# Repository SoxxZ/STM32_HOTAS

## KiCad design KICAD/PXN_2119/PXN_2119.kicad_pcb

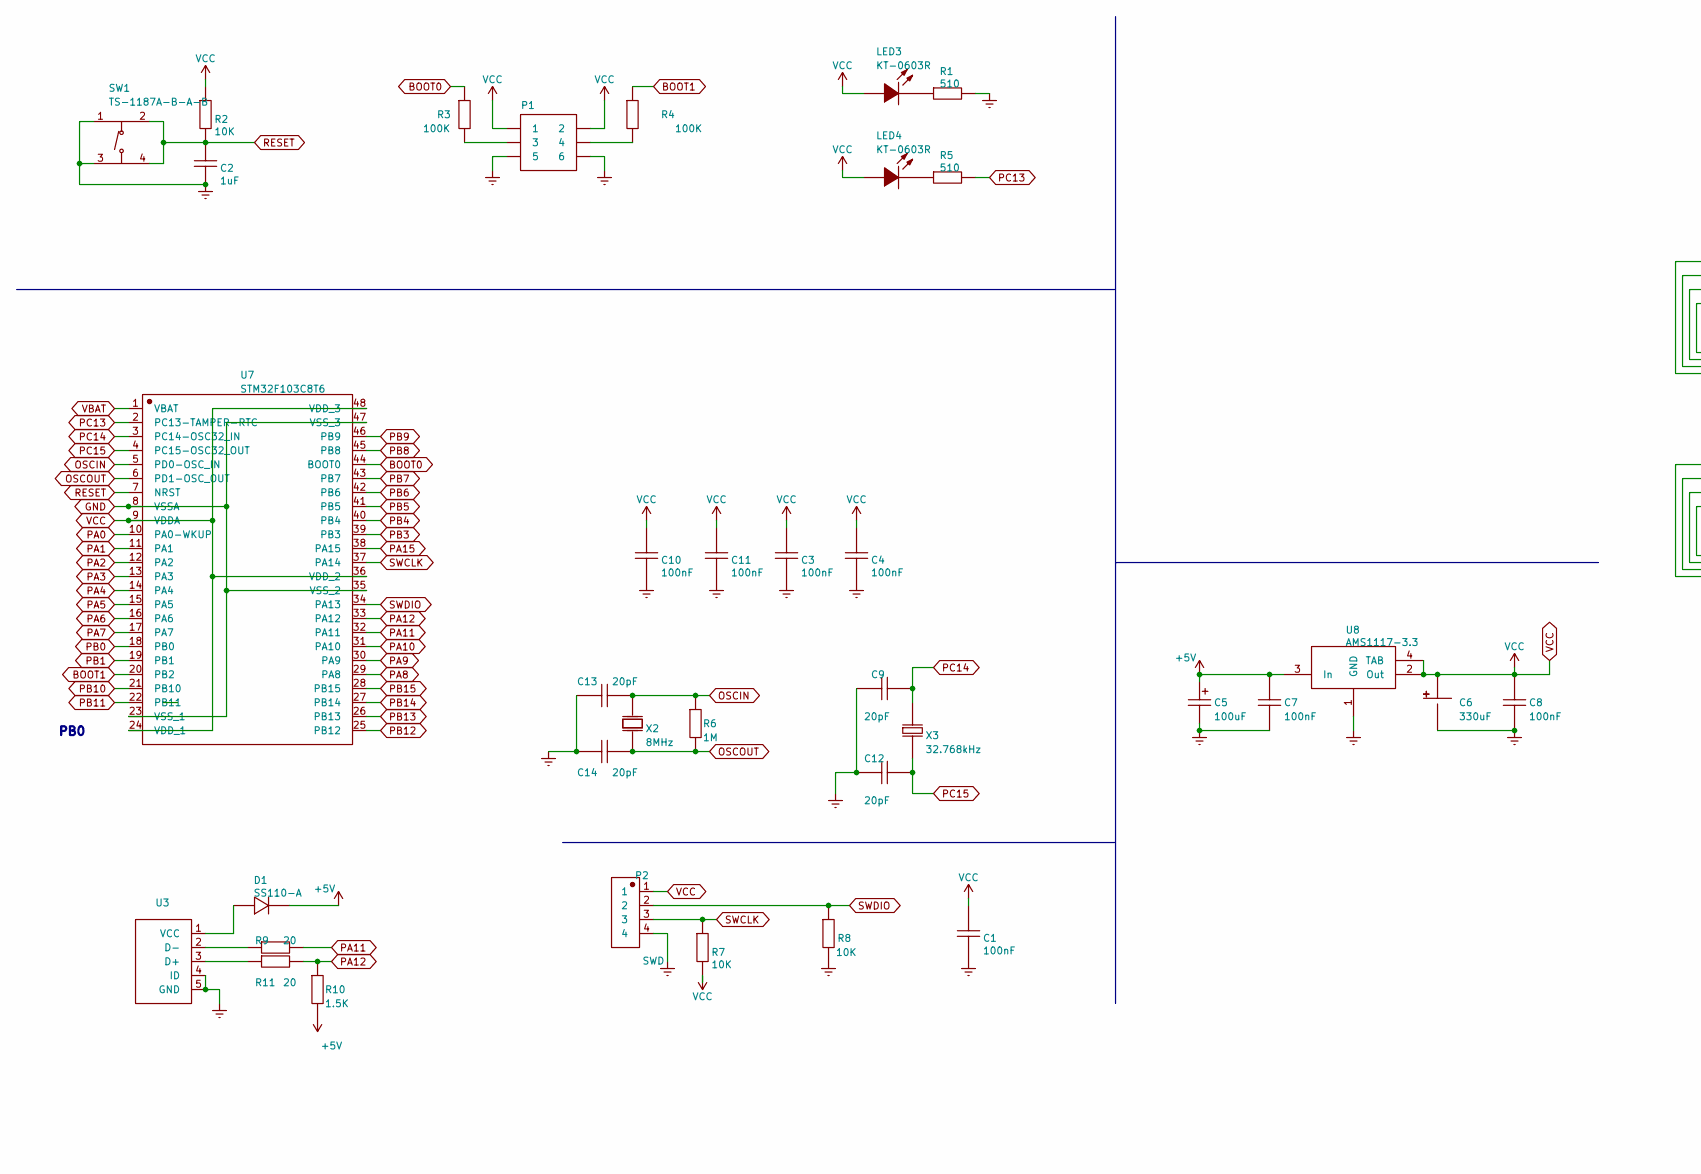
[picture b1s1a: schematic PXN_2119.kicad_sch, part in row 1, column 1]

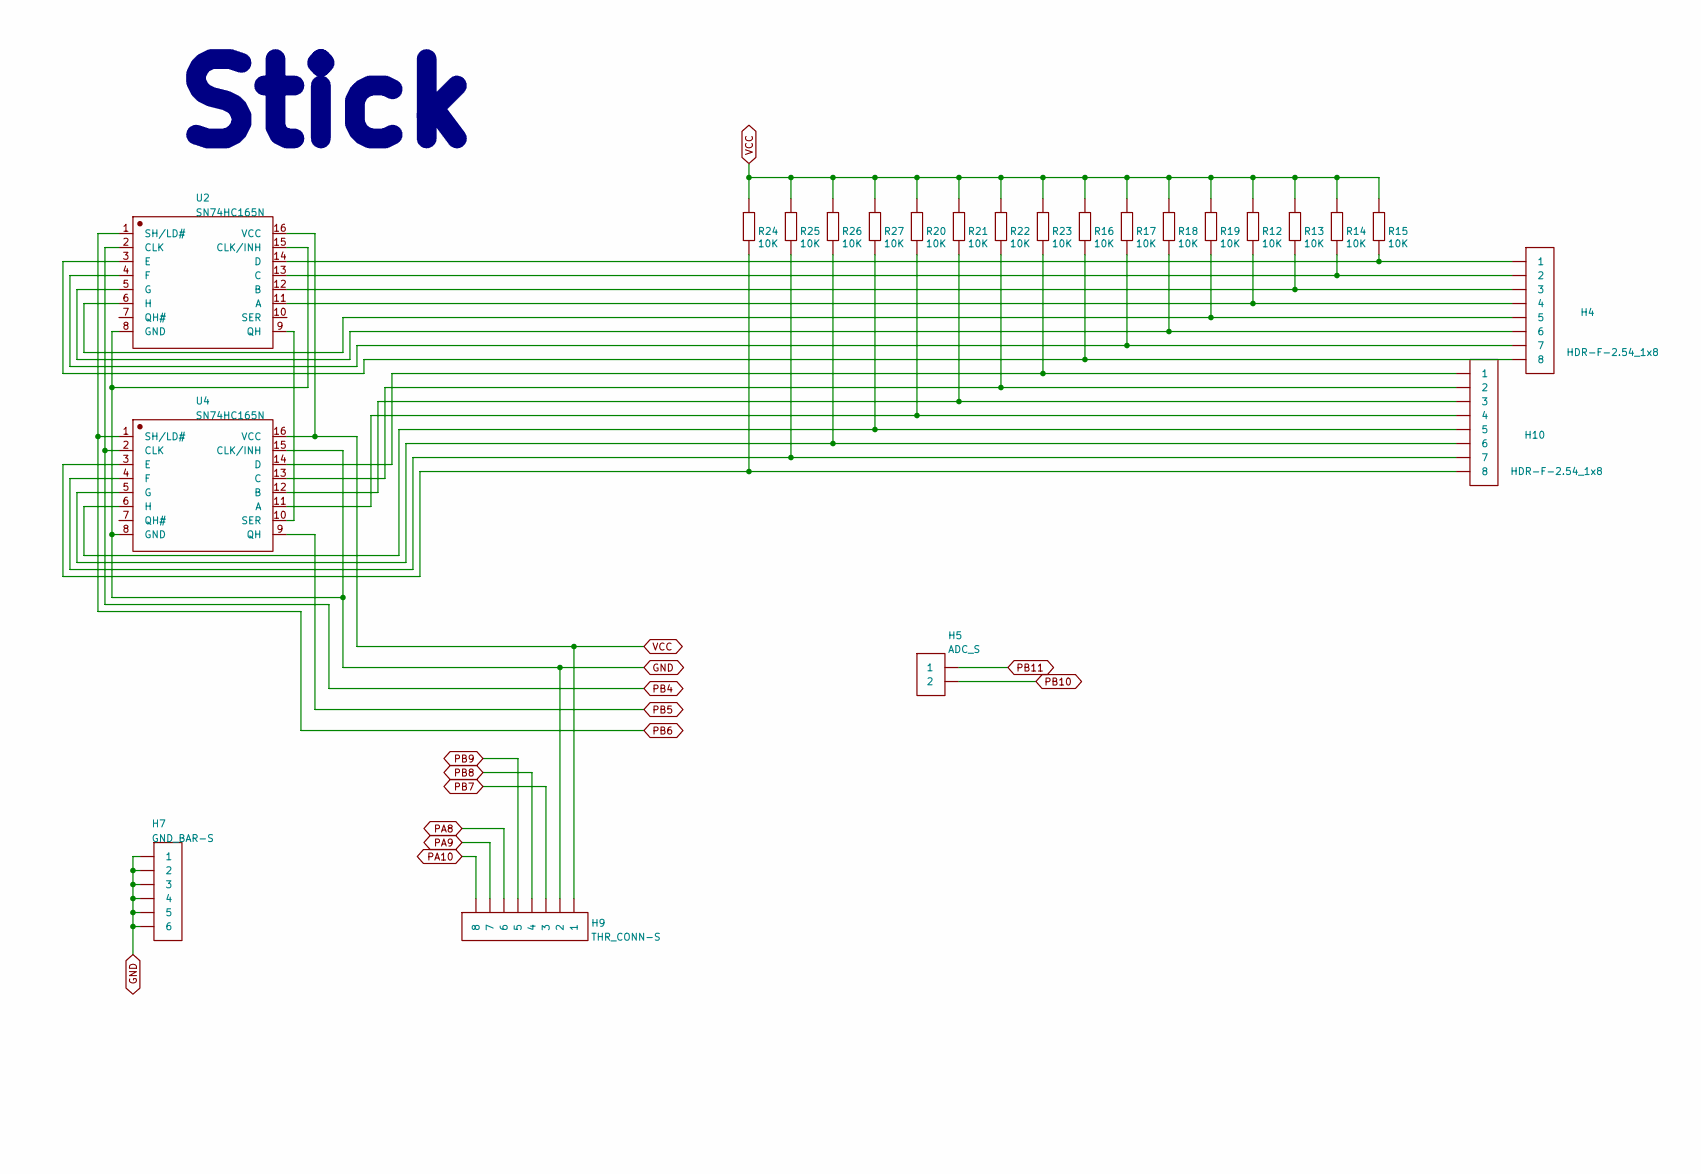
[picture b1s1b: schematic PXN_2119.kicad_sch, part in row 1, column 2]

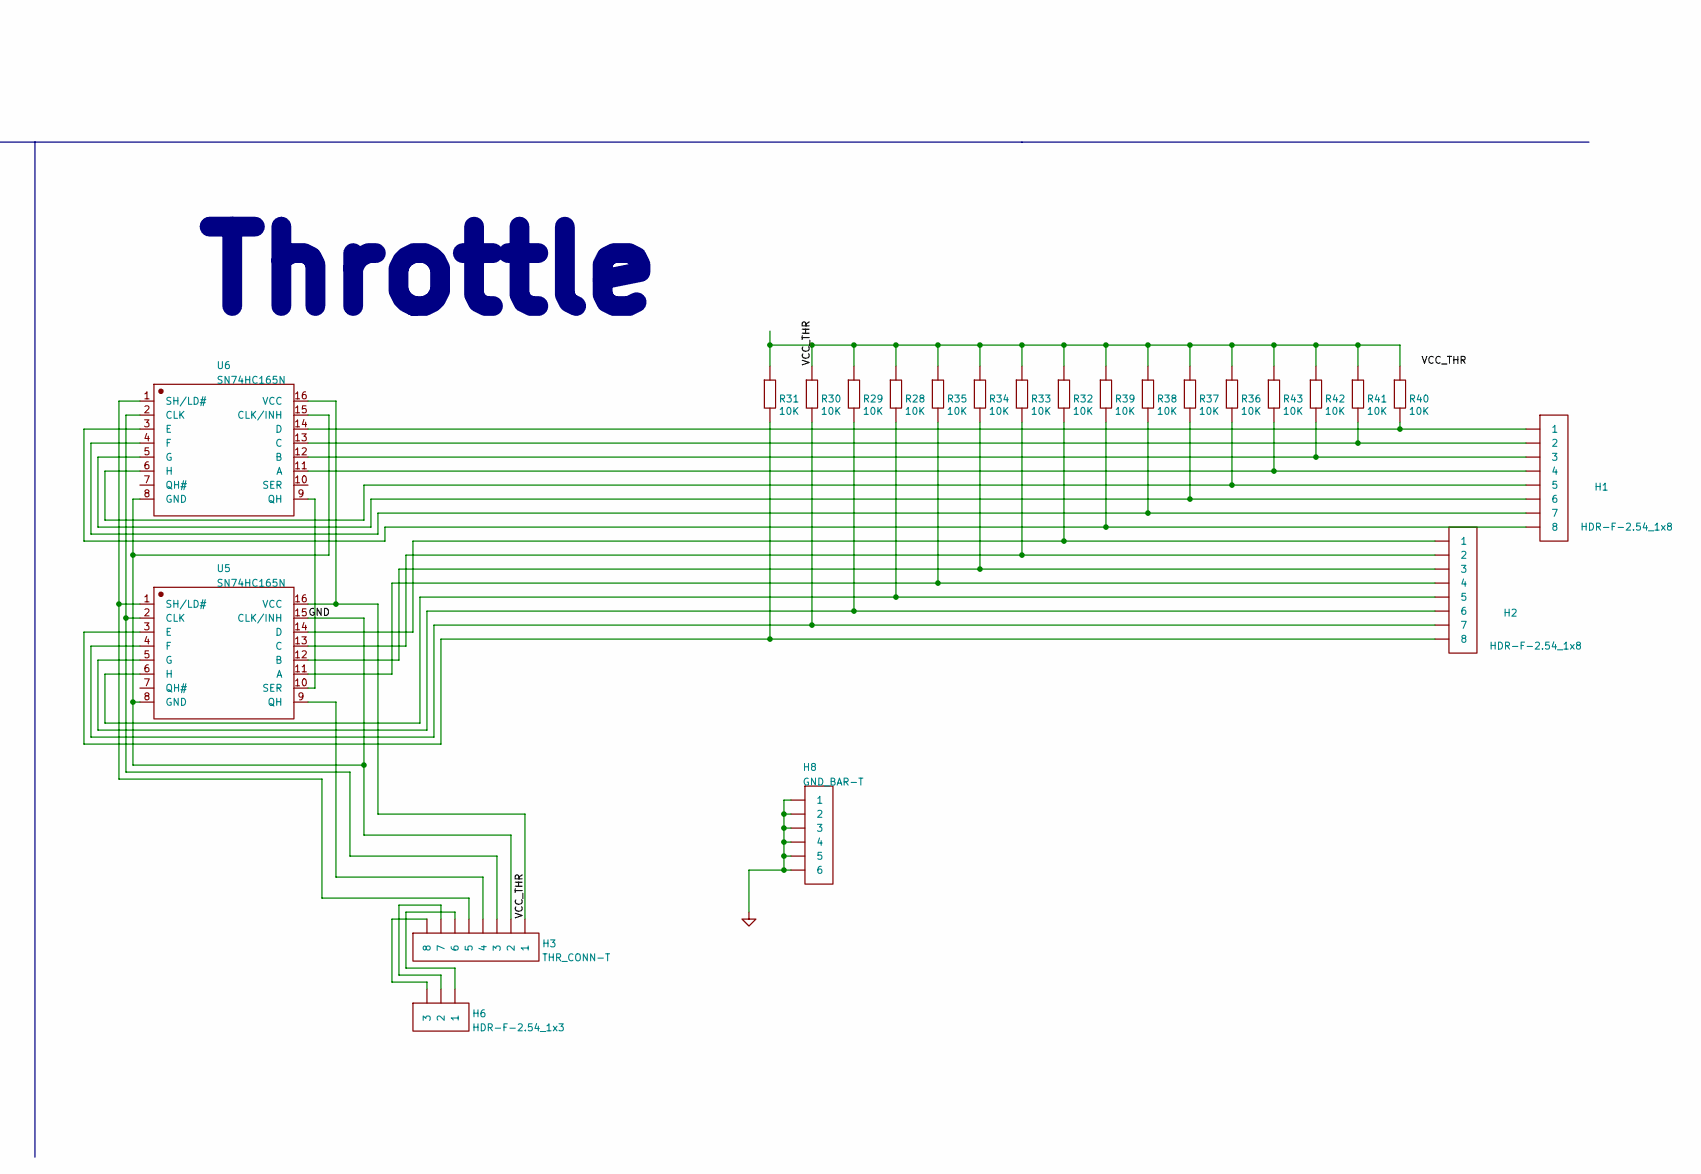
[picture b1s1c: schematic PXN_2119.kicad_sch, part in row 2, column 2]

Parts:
C1, C3, C4, C7, C8, C10, C11: 100nF; 0603_1608METRIC_PAD1.05X0.95MM_HANDSOLDER
C2: 1uF; 0603_1608METRIC_PAD1.05X0.95MM_HANDSOLDER
C5: 100uF; CASE-C_6032
C6: 330uF; CASE-C_6032
C9, C12, C13, C14: 20pF; 0603_1608METRIC_PAD1.05X0.95MM_HANDSOLDER
D1: SS110-A; SMA(DO-214AC)
H1, H2, H4, H10: HDR-F-2.54_1x8; HDR-F-2.54_1X8
H3: THR_CONN-T; HDR-F-2.54_1X8
H5: ADC_S; HDR-F-2.54_1X2
H6: HDR-F-2.54_1x3; HDR-F-2.54_1X3
H7: GND_BAR-S; HDR-F-2.54_1X6
H8: GND_BAR-T; HDR-F-2.54_1X6
H9: THR_CONN-S; HDR-F-2.54_1X8
LED3, LED4: KT-0603R; LED0603-R-RD
P1: HDR-IDC-2.54-2X3P; HEADER-2.54-P2x3
P2: SWD; HEADER-2.54-P4-ANG
R1, R5: 510; 0603_1608METRIC_PAD1.05X0.95MM_HANDSOLDER
R2, R7, R8, R12, R13, R14, R15, R16, R17, R18, R19, R20, R21, R22, R23, R24, R25, R26, R27, R28, R29, R30, R31, R32, R33, R34, R35, R36, R37, R38, R39, R40, R41, R42, R43: 10K; 0603_1608METRIC_PAD1.05X0.95MM_HANDSOLDER
R3, R4: 100K; 0603_1608METRIC_PAD1.05X0.95MM_HANDSOLDER
R6: 1M; 0603_1608METRIC_PAD1.05X0.95MM_HANDSOLDER
R9, R11: 20; 0603_1608METRIC_PAD1.05X0.95MM_HANDSOLDER
R10: 1.5K; 0603_1608METRIC_PAD1.05X0.95MM_HANDSOLDER
SW1: TS-1187A-B-A-B; SW-SMD_4P-L5.1-W5.1-P3.70-LS6.5-TL-2
U2, U4, U5, U6: SN74HC165N; DIP-16_L19.8-W6.5-P2.54-LS7.6-BL
U3: Micro USB-B 5P_C40942; USB-MICROB
U7: STM32F103C8T6; LQFP-48_L7.0-W7.0-P0.50-LS9.0-BL
U8: AMS1117-3.3; SOT-223
X2: 8MHz; CRYSTAL-SMD_L11.5-W4.8-LS12.7
X3: 32.768kHz; FC-135R_L3.2-W1.5

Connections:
+5V: C5.1, C7.2, D1.2, R10.2, U8.3 (In)
/VCC_THR: H3.1, R28.2, R29.2, R30.2, R31.2, R32.2, R33.2, R34.2, R35.2, R36.2, R37.2, R38.2, R39.2, R40.2, R41.2, R42.2, R43.2, U5.16 (VCC), U6.16 (VCC)
BOOT0: R3.1, U7.44 (BOOT0)
BOOT1: R4.1, U7.20 (PB2)
GND: C1.1, C2.1, C3.1, C4.1, C5.2, C6.2, C7.1, C8.1, C9.1, C10.1, C11.1, C12.1, C13.1, C14.1, H3.2, H7.1, H7.2, H7.3, H7.4, H7.5, H7.6, H8.1, H8.2, H8.3, H8.4, H8.5, H8.6, H9.2, P1.5, P1.6, P2.4, R1.2, R8.1, SW1.1 (A), SW1.3 (C), U2.8 (GND), U2.15 (CLK/INH), U3.4 (ID), U3.5 (GND), U4.8 (GND), U4.15 (CLK/INH), U5.8 (GND), U5.15 (CLK/INH), U6.8 (GND), U6.15 (CLK/INH), U7.8 (VSSA), U7.23 (VSS_1), U7.35 (VSS_2), U7.47 (VSS_3), U8.1 (GND)
unnamed: D1.1, U3.1 (VCC)
unnamed: H1.1, R40.1, U6.14 (D)
unnamed: H1.2, R41.1, U6.13 (C)
unnamed: H1.3, R42.1, U6.12 (B)
unnamed: H1.4, R43.1, U6.11 (A)
unnamed: H1.5, R36.1, U6.6 (H)
unnamed: H1.6, R37.1, U6.5 (G)
unnamed: H1.7, R38.1, U6.4 (F)
unnamed: H1.8, R39.1, U6.3 (E)
unnamed: H2.1, R32.1, U5.14 (D)
unnamed: H2.2, R33.1, U5.13 (C)
unnamed: H2.3, R34.1, U5.12 (B)
unnamed: H2.4, R35.1, U5.11 (A)
unnamed: H2.5, R28.1, U5.6 (H)
unnamed: H2.6, R29.1, U5.5 (G)
unnamed: H2.7, R30.1, U5.4 (F)
unnamed: H2.8, R31.1, U5.3 (E)
unnamed: H3.3, U5.2 (CLK), U6.2 (CLK)
unnamed: H3.4, U5.9 (QH)
unnamed: H3.5, U5.1 (SH/LD#), U6.1 (SH/LD#)
unnamed: H3.6, H6.1
unnamed: H3.7, H6.2
unnamed: H3.8, H6.3
unnamed: H4.1, R15.1, U2.14 (D)
unnamed: H4.2, R14.1, U2.13 (C)
unnamed: H4.3, R13.1, U2.12 (B)
unnamed: H4.4, R12.1, U2.11 (A)
unnamed: H4.5, R19.1, U2.6 (H)
unnamed: H4.6, R18.1, U2.5 (G)
unnamed: H4.7, R17.1, U2.4 (F)
unnamed: H4.8, R16.1, U2.3 (E)
unnamed: H10.1, R23.1, U4.14 (D)
unnamed: H10.2, R22.1, U4.13 (C)
unnamed: H10.3, R21.1, U4.12 (B)
unnamed: H10.4, R20.1, U4.11 (A)
unnamed: H10.5, R27.1, U4.6 (H)
unnamed: H10.6, R26.1, U4.5 (G)
unnamed: H10.7, R25.1, U4.4 (F)
unnamed: H10.8, R24.1, U4.3 (E)
unnamed: LED3.2 (K), R1.1
unnamed: LED4.2 (K), R5.1
unnamed: P1.3, R3.2
unnamed: P1.4, R4.2
unnamed: R9.1, U3.2 (D-)
unnamed: R11.1, U3.3 (D+)
unnamed: U2.9 (QH), U4.10 (SER)
unnamed: U5.10 (SER), U6.9 (QH)
OSCIN: C13.2, R6.2, U7.5 (PD0-OSC_IN), X2.1 (OSC1)
OSCOUT: C14.2, R6.1, U7.6 (PD1-OSC_OUT), X2.2 (OSC2)
PA0: U7.10 (PA0-WKUP)
PA1: U7.11 (PA1)
PA2: U7.12 (PA2)
PA3: U7.13 (PA3)
PA4: U7.14 (PA4)
PA5: U7.15 (PA5)
PA6: U7.16 (PA6)
PA7: U7.17 (PA7)
PA8: H9.6, U7.29 (PA8)
PA9: H9.7, U7.30 (PA9)
PA10: H9.8, U7.31 (PA10)
PA11: R9.2, U7.32 (PA11)
PA12: R10.1, R11.2, U7.33 (PA12)
PA15: U7.38 (PA15)
PB0: U7.18 (PB0)
PB1: U7.19 (PB1)
PB3: U7.39 (PB3)
PB4: U2.2 (CLK), U4.2 (CLK), U7.40 (PB4)
PB5: U4.9 (QH), U7.41 (PB5)
PB6: U2.1 (SH/LD#), U4.1 (SH/LD#), U7.42 (PB6)
PB7: H9.3, U7.43 (PB7)
PB8: H9.4, U7.45 (PB8)
PB9: H9.5, U7.46 (PB9)
PB10: H5.2, U7.21 (PB10)
PB11: H5.1, U7.22 (PB11)
PB12: U7.25 (PB12)
PB13: U7.26 (PB13)
PB14: U7.27 (PB14)
PB15: U7.28 (PB15)
PC13: R5.2, U7.2 (PC13-TAMPER-RTC)
PC14: C9.2, U7.3 (PC14-OSC32_IN), X3.2
PC15: C12.2, U7.4 (PC15-OSC32_OUT), X3.1
RESET: C2.2, R2.1, SW1.2 (B), SW1.4 (D), U7.7 (NRST)
SWCLK: P2.3, R7.2, U7.37 (PA14)
SWDIO: P2.2, R8.2, U7.34 (PA13)
VBAT: U7.1 (VBAT)
VCC: C1.2, C3.2, C4.2, C6.1, C8.2, C10.2, C11.2, H9.1, LED3.1 (A), LED4.1 (A), P1.1, P1.2, P2.1, R2.2, R7.1, R12.2, R13.2, R14.2, R15.2, R16.2, R17.2, R18.2, R19.2, R20.2, R21.2, R22.2, R23.2, R24.2, R25.2, R26.2, R27.2, U2.16 (VCC), U4.16 (VCC), U7.9 (VDDA), U7.24 (VDD_1), U7.36 (VDD_2), U7.48 (VDD_3), U8.2 (Out), U8.4 (TAB)

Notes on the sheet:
PB0
Stick
Throttle

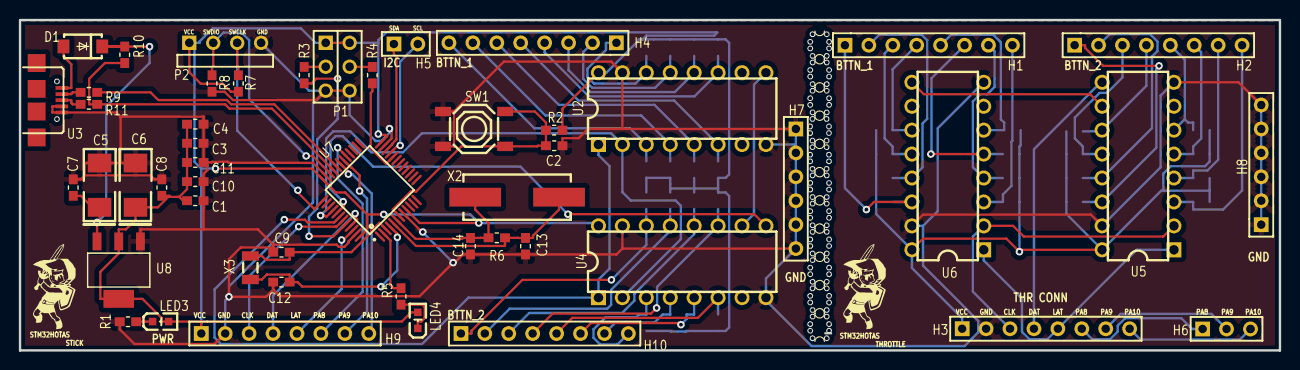
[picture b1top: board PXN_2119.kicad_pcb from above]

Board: 2 copper layers, 133.8 x 35.1 mm, 93 parts (0 on the bottom side), 74 nets.

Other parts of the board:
mouse-bite-1mm-slot-1, mouse-bite-1mm-slot-2, mouse-bite-1mm-slot-3, mouse-bite-1mm-slot-4, mouse-bite-1mm-slot-5, mouse-bite-1mm-slot-6, mouse-bite-1mm-slot-7, mouse-bite-1mm-slot-8, mouse-bite-1mm-slot-9, mouse-bite-1mm-slot-10, mouse-bite-1mm-slot-11: VAL**; mouse-bite-1mm-slot

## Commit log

2022-04-27 editing_folders
2022-04-27 Updating 3D Models References
2022-04-27 Fixing Routing
2022-05-04 updating pcb
2022-05-04 adding gerber files
